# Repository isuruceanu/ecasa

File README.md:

ecasa - Home automation project
==============================

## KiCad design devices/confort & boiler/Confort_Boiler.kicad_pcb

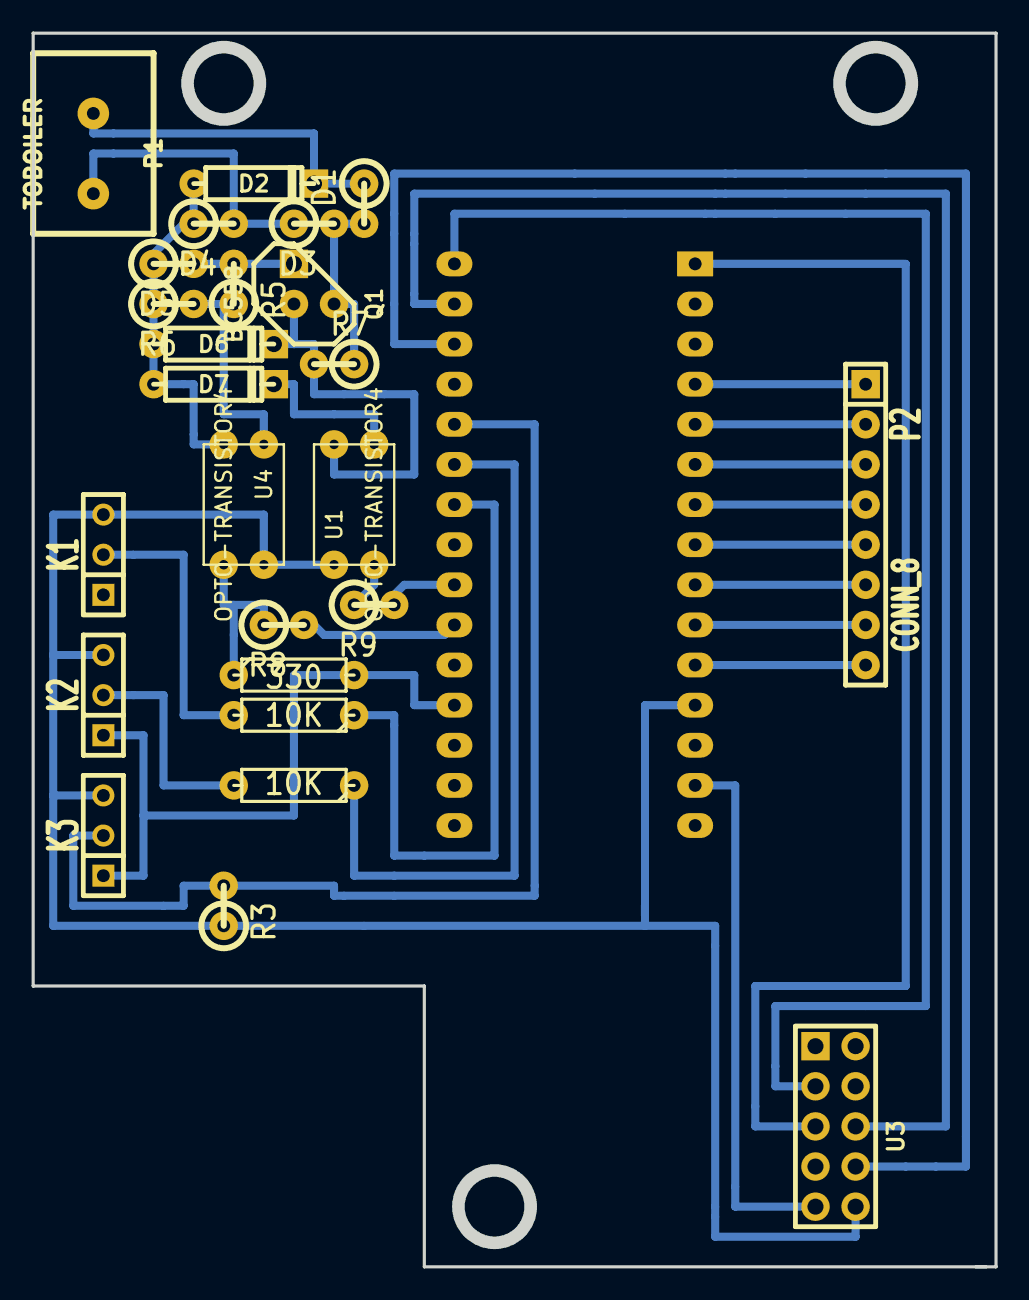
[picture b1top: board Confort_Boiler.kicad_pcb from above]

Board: 2 copper layers, 60.4 x 77.5 mm, 26 parts (1 on the bottom side), 31 nets.

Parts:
D1, D3, D4: DIODE; R1
D2: DIODE; D3
D5: 4v7; R1
D6: 15V; D3
D7: 4v3; D3
K1: DHT1; SIL-3
K2: DHT2; SIL-3
K3: DS18B20; SIL-3
P1: TOBOILER; DG306-5.08-02
P2: CONN_8; SIL-8
Q1: BC558; TO92
R1, R2: 10K; R3
R3: 4K7; R1
R4: 330; R3
R5: 200; R1
R6: 100; R1
R7: 330; R1
R8, R9: 1K5; R1
U1, U4: OPTO-TRANSISTOR4; PC817
U2: ARDUINO_MINI; arduino_mini
U3: ENC28J60; PIN_ARRAY_5x2

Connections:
GND: K1.1, K2.1, K3.1, R4.2, U2.14, U2.19, U3.9
LDHT1: R1.1, U2.24
LDHT2: R2.1, U2.25
LDS18B20: K3.2, R3.2, U2.26
LRX: R8.2, U2.21
LTX: R9.2, U2.22
unnamed: U2.28, U3.8
unnamed: U2.29, U3.6
unnamed: U2.30, U3.3
unnamed: U2.1, U3.5
unnamed: D1.1, D2.2, P1.2
unnamed: K1.2, R1.2
unnamed: K2.2, R2.2
unnamed: P2.1, U2.4
unnamed: R4.1, R8.1, U4.3
unnamed: R9.1, U1.2
unnamed: P2.2, U2.5
unnamed: P2.3, U2.6
unnamed: P2.4, U2.7
unnamed: P2.5, U2.8
unnamed: P2.6, U2.9
unnamed: P2.7, U2.10
unnamed: P2.8, U2.11
unnamed: D7.2, U1.3
unnamed: D5.2, Q1.1, R5.2
unnamed: D6.2, Q1.2, R7.2, U1.4
unnamed: D2.1, D4.1, D5.1, D6.1, D7.1, R6.1, U4.2
unnamed: R5.1, R6.2, U4.1
unnamed: D3.1, D4.2, P1.1
unnamed: D1.2, D3.2, Q1.3, R7.1
VCC: K1.3, K2.3, K3.3, R3.1, U1.1, U2.12, U3.10, U4.4

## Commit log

2014-11-25 second commit
2014-12-04 added opentherm gateway simulation
2014-12-10 Added Manchester code encode, decode is not tested yet
2014-12-10 moved manchester to own folder. here will test the ,anchester code, transmiter and receiver
2014-12-10 added ignore file
2014-12-10 added isis proteus test file, added more ext on ignore
2014-12-21 added atmel studio project
2015-01-08 added rs485 implementation
2015-01-18 added web server
2015-01-20 added devices page, work in progress
2015-01-22 separate handlers into own files: controllers
2015-01-22 added websocket
2015-02-12 added Confort&Boiler device kicad project
2015-02-16 update to latest code
2015-02-16 added missing lib file
2015-03-04 modified the boiler schema in order to use Open Therm
2015-03-28 pcb for boiler almost done
2015-03-29 finished with pcb
2015-03-29 added modules
2015-03-29 checked the pcb with real components and made according adjusments
2015-03-30 added analog port as output for future use, changed dgs connectors to sil
2015-11-02 removed unused files
2015-11-03 added Termostat.ino
2015-12-24 removed old project
2015-12-24 removed old project files
2015-12-24 created beego template project
2015-12-24 added Docker file
2016-01-25 start development
2016-01-25 added temperature test reader
2016-01-25 migrate to new beego and added godeps
2016-02-02 added dht pure implmentation
2016-02-02 test for dht
